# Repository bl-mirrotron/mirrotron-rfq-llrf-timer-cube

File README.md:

# RFQ LLRF Timer Cube
* <a href="https://github.com/bl-mirrotron/mirrotron-rfq-llrf-timer-cube" target="_blank">Source code</a>
* [RF frequency source](https://bl-mirrotron.github.io/mirrotron-rf-src-tray/)
* [Gate generator](https://bl-mirrotron.github.io/gateGen125-tray/)
* [Timing system overview](https://bl-mirrotron.github.io/#timing-system)
* [Control system overview](https://bl-mirrotron.github.io/)

The RFQ LLRF Timer Cube is a circuit card that mounts onto header connectors of a <a href="https://redpitaya.com/product-category/stemlab-125-14/" target="_blank">Red Pitaya Stemlab 125-14</a> computer  as shown in Figure 1.  The circuit is used both for the <a href="https://bl-mirrotron.github.io/mirrotron-rf-src-tray/">RF Frequency Source</a> and the <a href="https://bl-mirrotron.github.io/gateGen125-tray/">Gate Generator</a> for the <a href="https://bl-mirrotron.github.io/#timing-system">Timing system</a>. The card contains two systems that can be used independently.

The first system connects a <a href="https://www.mikroe.com/pll-click" target="_blank">PLL Click</a> 8x Phase Lock Loop card that is used by the RF Frequency Source to multiply the 12.5 MHz Direct Digital Synthesizer signal from the Red Pitaya Stemlab 125-14 to 100 MHz.

The second system generates TTL level signals from the Red Pitaya Stemlab 125-14 FPGA digital output pin header to eight SMA RF connectors for the Gate Generator  used in the Timing system.

The circuit also provides 5V and 3.3V output from the Red Pitaya Stemlab 125-14 that can be used to power auxiliary devices such as micro-fans or low noise amplifiers.

The schematic for the card is shown in Figure 2 and the PCB layout is shown in Figure 3.

<p style="text-align:center;font-size: large;"><span style="font-weight: bold;color: green;">Figure 1. </span> <span style="font-style: italic;">RFQ LLRF Timer Cube mounted on a Red Pitaya Stemlab 125-14</span></p>
<div style="width:100%;text-align:center;"></div><br>

<p style="text-align:center;font-size: large;"><span style="font-weight: bold;color: green;">Figure 2. </span> <span style="font-style: italic;">RFQ LLRF Timer Cube Schematic</span></p>
<div style="width:100%;text-align:center;"></div><br>

<p style="text-align:center;font-size: large;"><span style="font-weight: bold;color: green;">Figure 3. </span> <span style="font-style: italic;">RFQ LLRF Timer Cube PCB layout</span></p>
<div style="width:100%;text-align:center;"></div><br>

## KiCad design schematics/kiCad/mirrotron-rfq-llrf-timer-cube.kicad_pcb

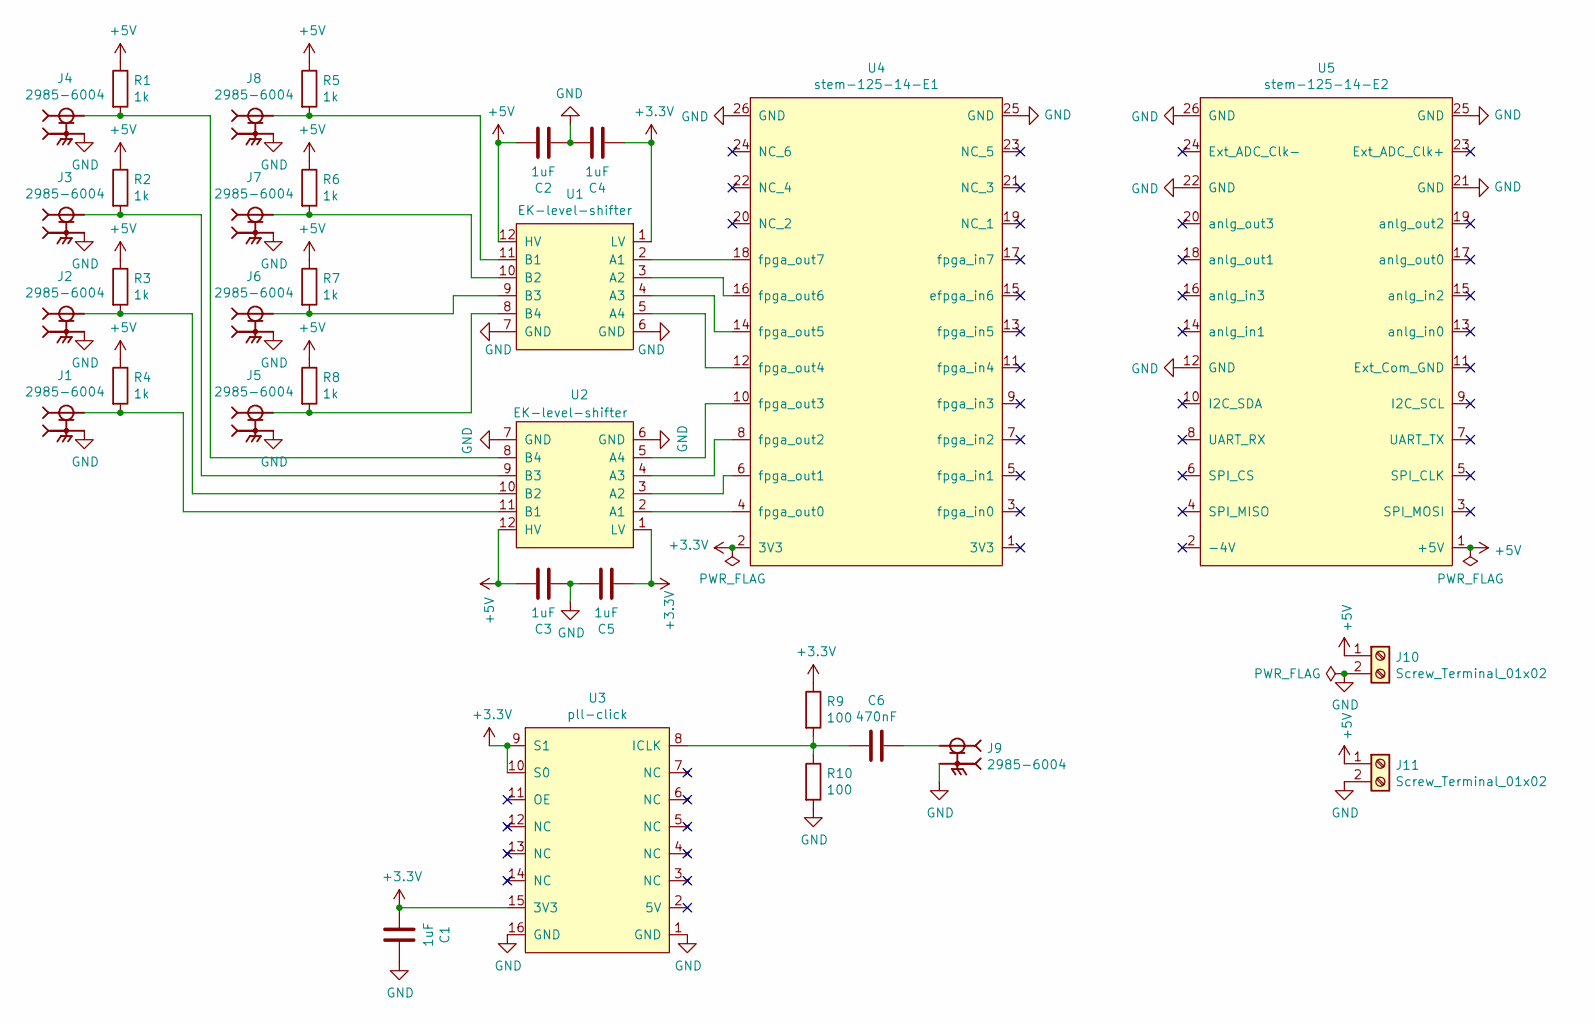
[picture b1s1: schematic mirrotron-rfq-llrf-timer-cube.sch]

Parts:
C1, C2, C3, C4, C5: 1uF; C_1206_3216Metric_Pad1.33x1.80mm_HandSolder
C6: 470nF; C_1206_3216Metric_Pad1.33x1.80mm_HandSolder
J1, J2, J3, J4, J5, J6, J7, J8, J9: 2985-6004; AMPHENOL_2985-6004
J10, J11: Screw_Terminal_01x02; TerminalBlock_bornier-2_P5.08mm
R1, R2, R3, R4, R5, R6, R7, R8: 1k; R_1206_3216Metric_Pad1.30x1.75mm_HandSolder
R9, R10: 100; R_1206_3216Metric_Pad1.30x1.75mm_HandSolder
U1, U2: EK-level-shifter
U3: pll-click
U4: stem-125-14-E1; red-pitaya-extender
U5: stem-125-14-E2; red-pitaya-extender

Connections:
+3V3: C1.2, C4.2, C5.2, R9.1, U1.1 (LV), U2.1 (LV), U3.9 (S1), U3.10 (S0), U3.15 (3V3), U4.2 (3V3)
+5V: C2.1, C3.1, J10.1, J11.1, R1.1, R2.1, R3.1, R4.1, R5.1, R6.1, R7.1, R8.1, U1.12 (HV), U2.12 (HV), U5.1 (+5V)
GND: C1.1, C2.2, C3.2, C4.1, C5.1, J1.S1, J1.S2, J1.S3, J1.S4, J2.S1, J2.S2, J2.S3, J2.S4, J3.S1, J3.S2, J3.S3, J3.S4, J4.S1, J4.S2, J4.S3, J4.S4, J5.S1, J5.S2, J5.S3, J5.S4, J6.S1, J6.S2, J6.S3, J6.S4, J7.S1, J7.S2, J7.S3, J7.S4, J8.S1, J8.S2, J8.S3, J8.S4, J9.S1, J9.S2, J9.S3, J9.S4, J10.2, J11.2, R10.2, U1.6 (GND), U1.7 (GND), U2.6 (GND), U2.7 (GND), U3.1 (GND), U3.16 (GND), U4.25 (GND), U4.26 (GND), U5.12 (GND), U5.21 (GND), U5.22 (GND), U5.25 (GND), U5.26 (GND)
unnamed: C6.1, J9.1
unnamed: C6.2, R9.2, R10.1, U3.8 (ICLK)
unnamed: J1.1, R4.2, U2.11 (B1)
unnamed: J2.1, R3.2, U2.10 (B2)
unnamed: J3.1, R2.2, U2.9 (B3)
unnamed: J4.1, R1.2, U2.8 (B4)
unnamed: J5.1, R8.2, U1.8 (B4)
unnamed: J6.1, R7.2, U1.9 (B3)
unnamed: J7.1, R6.2, U1.10 (B2)
unnamed: J8.1, R5.2, U1.11 (B1)
unnamed: U1.2 (A1), U4.18 (fpga_out7)
unnamed: U1.3 (A2), U4.16 (fpga_out6)
unnamed: U1.4 (A3), U4.14 (fpga_out5)
unnamed: U1.5 (A4), U4.12 (fpga_out4)
unnamed: U2.2 (A1), U4.4 (fpga_out0)
unnamed: U2.3 (A2), U4.6 (fpga_out1)
unnamed: U2.4 (A3), U4.8 (fpga_out2)
unnamed: U2.5 (A4), U4.10 (fpga_out3)

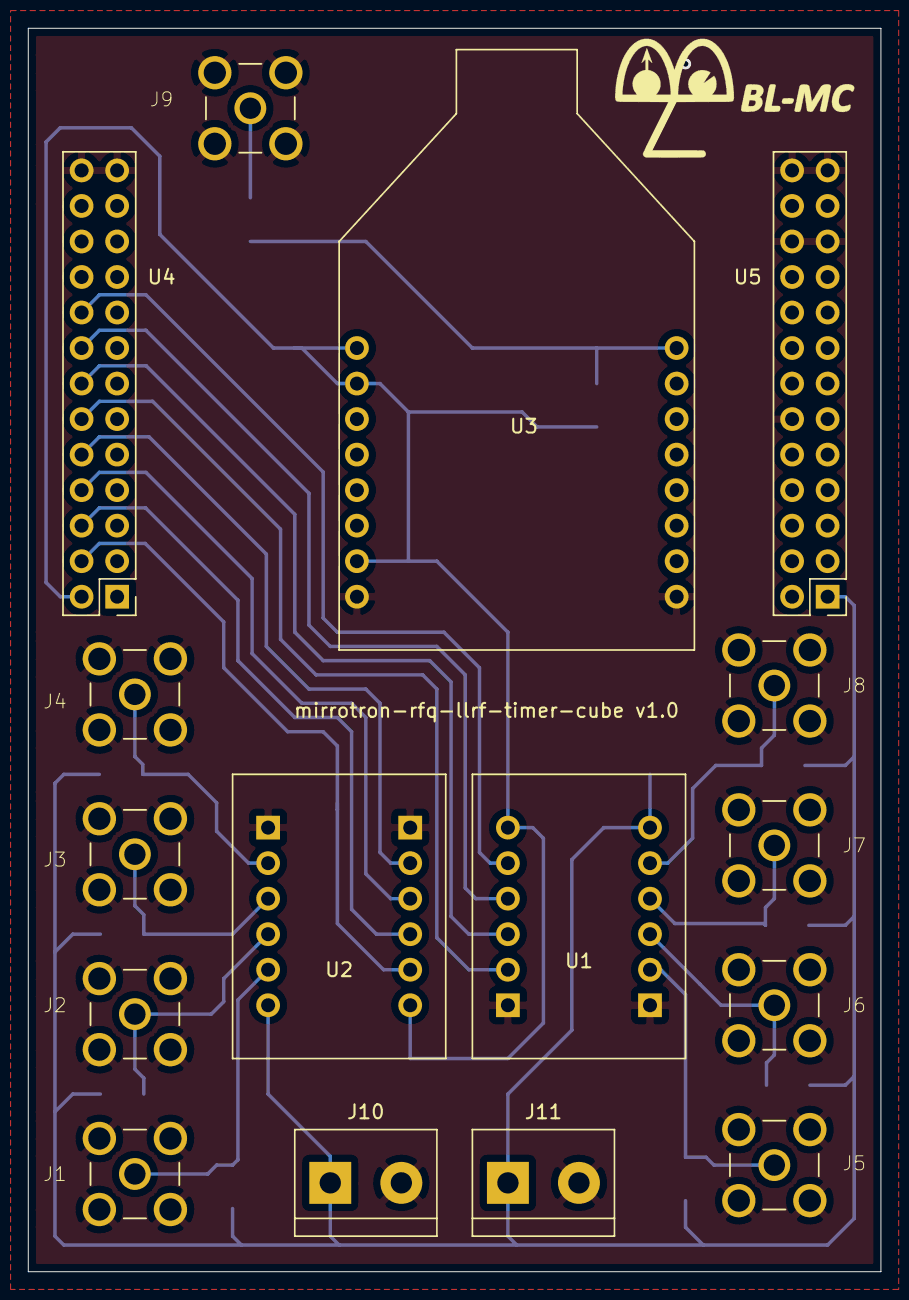
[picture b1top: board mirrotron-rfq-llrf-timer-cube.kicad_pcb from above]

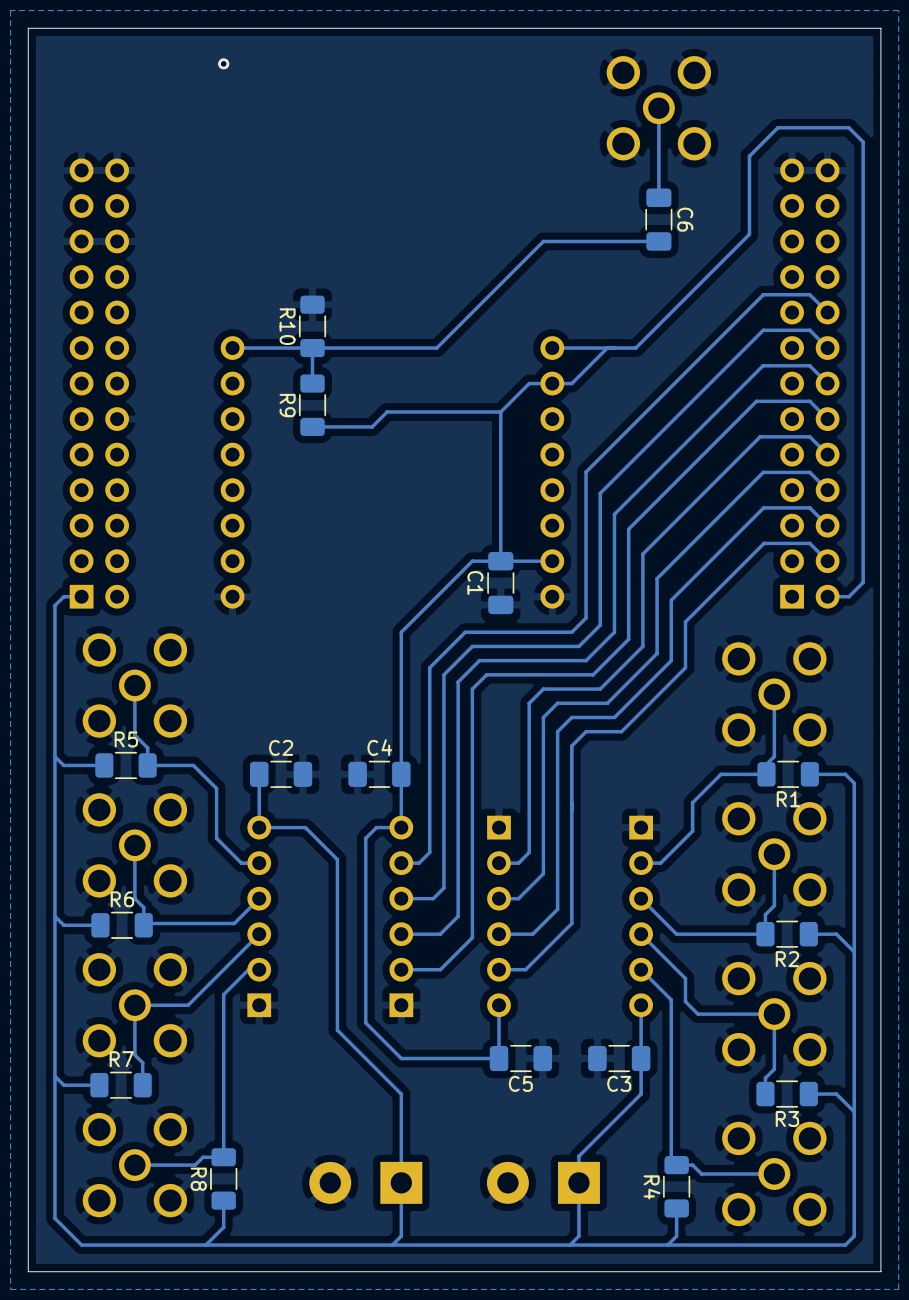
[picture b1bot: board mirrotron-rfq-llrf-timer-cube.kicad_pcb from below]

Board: 2 copper layers, 61.0 x 88.9 mm, 32 parts (16 on the bottom side), 21 nets.

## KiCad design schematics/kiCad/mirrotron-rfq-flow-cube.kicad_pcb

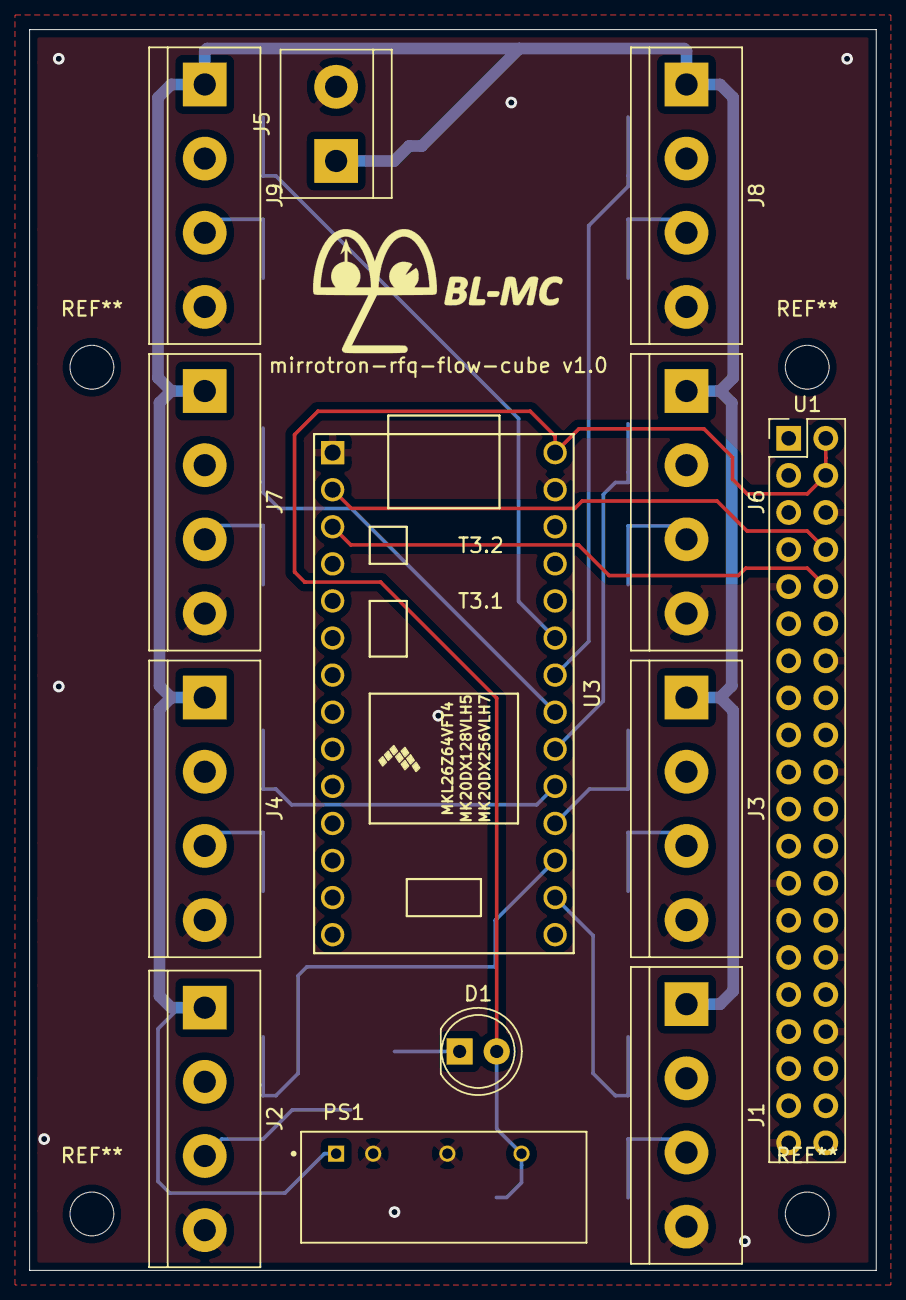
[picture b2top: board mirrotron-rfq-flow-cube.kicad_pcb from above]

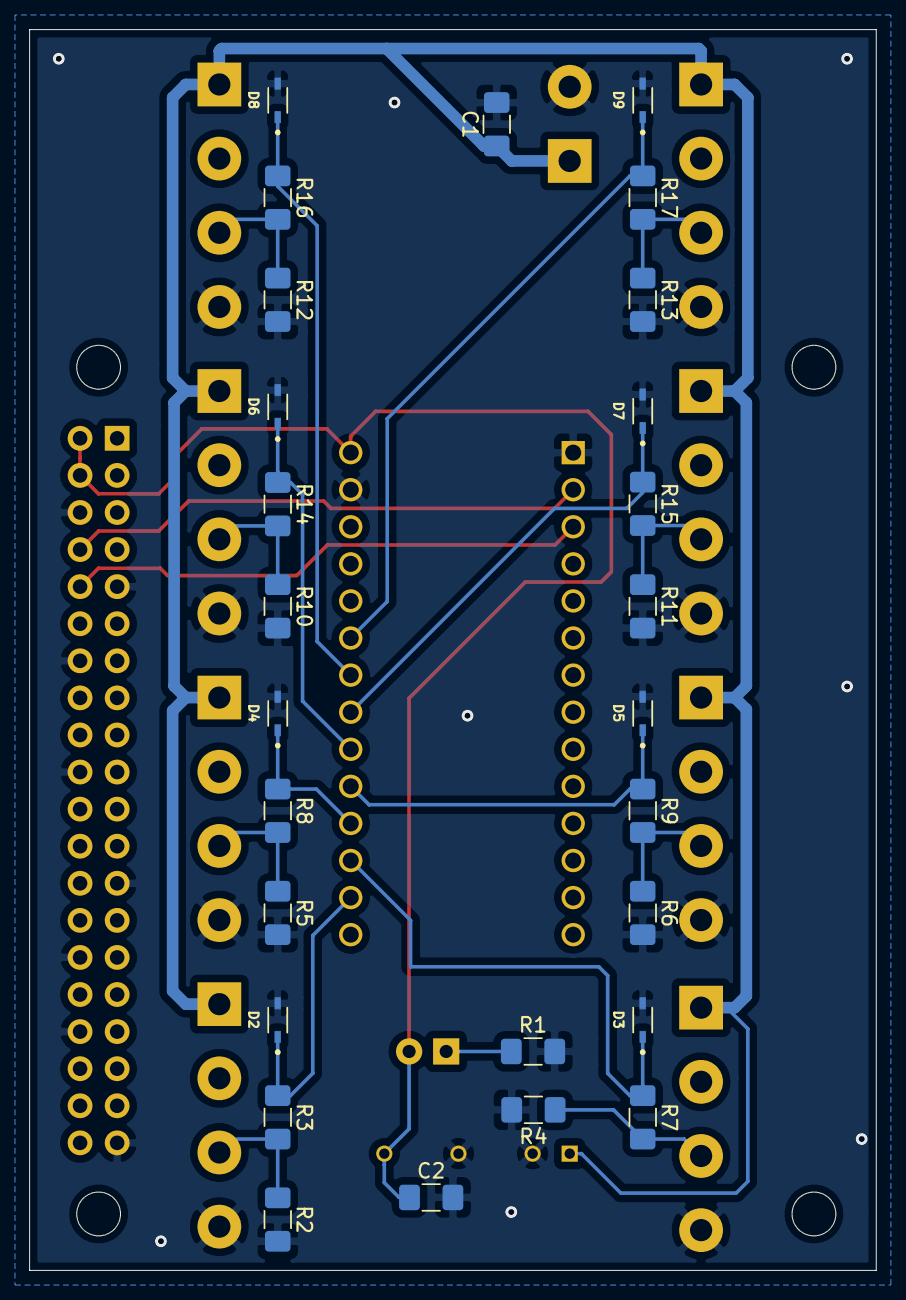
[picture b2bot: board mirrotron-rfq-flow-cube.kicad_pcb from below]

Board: 2 copper layers, 58.0 x 85.0 mm, 40 parts (27 on the bottom side), 22 nets.

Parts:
C1, C2: 1uF; C_1206_3216Metric_Pad1.42x1.75mm_HandSolder
D1: GREEN; LED_D5.0mm
D2, D3, D4, D5, D6, D7, D8, D9: 3.3; SODFL2513X100N
J1, J2, J3, J4, J6, J7, J8, J9: Screw_Terminal_01x04; TerminalBlock_bornier-4_P5.08mm
J5: Screw_Terminal_01x02; TerminalBlock_bornier-2_P5.08mm
PS1: TBA_2-2411; CONV_TBA_2-2411
R1: 220; R_1206_3216Metric_Pad1.42x1.75mm_HandSolder
R2, R3, R4, R5, R6, R7, R8, R9, R10, R11, R12, R13, R14, R15, R16, R17: 100; R_1206_3216Metric_Pad1.42x1.75mm_HandSolder
U1: RPIHeader; PinHeader_2x20_P2.54mm_Vertical
U3: Teensy-LC; Teensy30_31_32_LC

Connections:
+5V: C2.1, D1.2, PS1.6, U1.2, U1.4, U3.33
+24V: C1.1, J1.1, J2.1, J3.1, J4.1, J5.1, J6.1, J7.1, J8.1, J9.1, PS1.1
/P14: D2.1, R3.1, U3.21
/P15: D3.1, R7.1, U3.22
/P16: D4.1, R8.1, U3.23
/P17: D5.1, R9.1, U3.24
/P18: D6.1, R14.1, U3.25
/P19: D7.1, R15.1, U3.26
/P20: D8.1, R16.1, U3.27
/P21: D9.1, R17.1, U3.28
GND: C1.2, C2.2, D2.2, D3.2, D4.2, D5.2, D6.2, D7.2, D8.2, D9.2, J1.4, J2.4, J3.4, J4.4, J5.2, J6.4, J7.4, J8.4, J9.4, PS1.2, PS1.4, R1.2, R2.2, R4.2, R5.2, R6.2, R10.2, R11.2, R12.2, R13.2, U1.6, U1.9, U1.14, U1.20, U1.25, U1.30, U1.34, U1.39, U3.1, U3.32
unnamed: D1.1, R1.1
unnamed: J1.3, R2.1, R3.2
unnamed: J2.3, R4.1, R7.2
unnamed: J3.3, R5.1, R8.2
unnamed: J4.3, R6.1, R9.2
unnamed: J6.3, R10.1, R14.2
unnamed: J7.3, R11.1, R15.2
unnamed: J8.3, R12.1, R16.2
unnamed: J9.3, R13.1, R17.2
unnamed: U1.8, U3.2
unnamed: U1.10, U3.3

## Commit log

2022-03-31 circuit board designed
2022-08-05 added doc
2022-08-11 Set theme jekyll-theme-tactile
